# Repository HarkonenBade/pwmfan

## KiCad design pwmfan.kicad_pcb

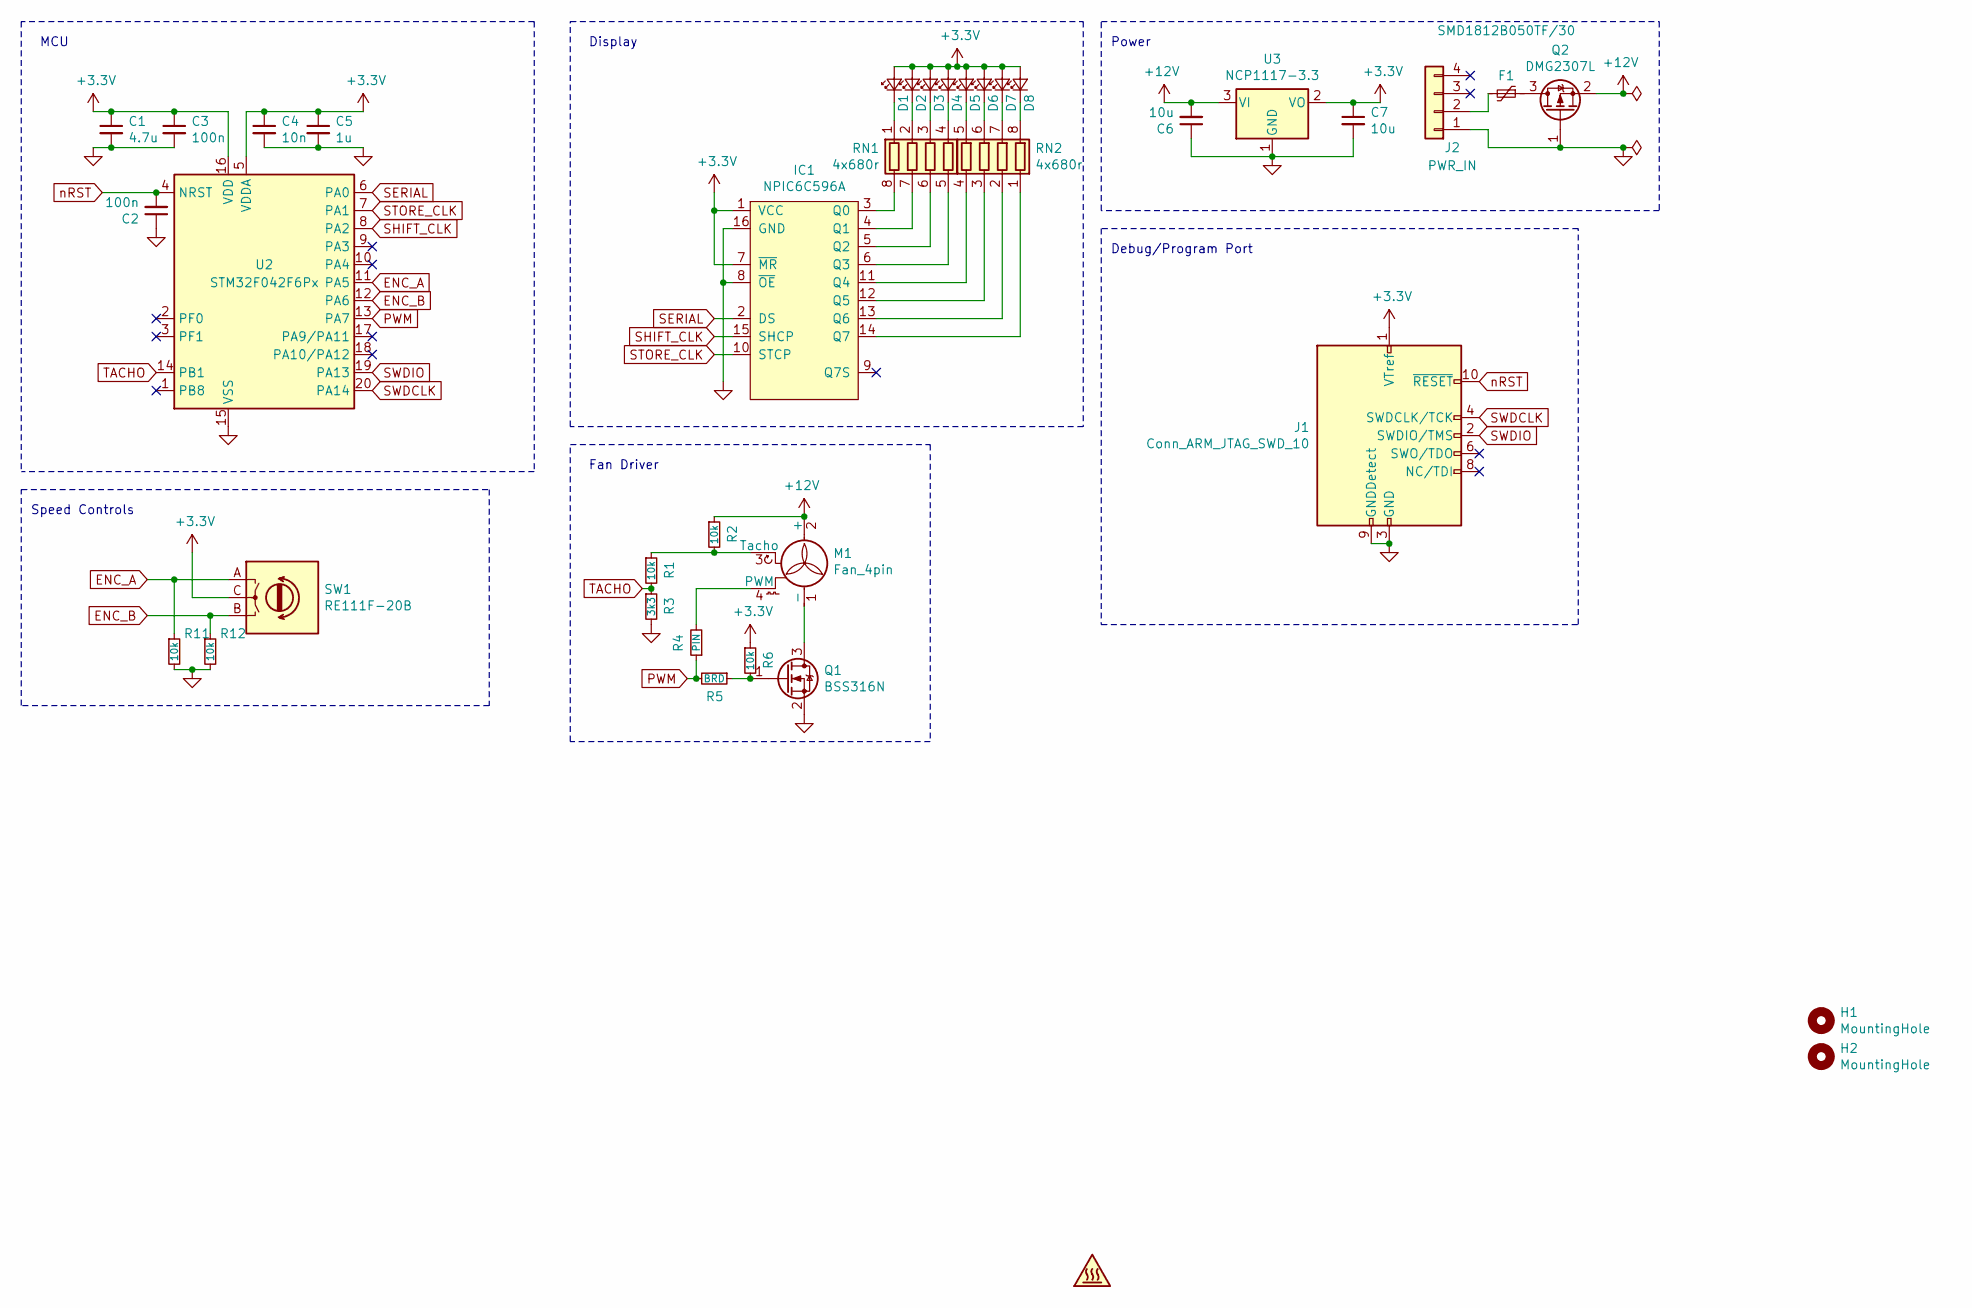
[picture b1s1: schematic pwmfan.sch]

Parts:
C1: 4.7u; C_0603_1608Metric
C2, C3: 100n; C_0603_1608Metric
C4: 10n; C_0603_1608Metric
C5: 1u; C_0603_1608Metric
C6, C7: 10u; C_0603_1608Metric
D1, D2, D3, D4, D5, D6, D7, D8: LED_Small; LED_D3.0mm_Horizontal_O1.27mm_Z2.0mm
F1: SMD1812B050TF/30; Fuse_1812_4532Metric; Farnell 3052512
H1, H2: MountingHole; MountingHole_3.2mm_M3_Pad
IC1: NPIC6C596A; TSSOP-16_4.4x5mm_P0.65mm; Farnell 2445196
J1: Conn_ARM_JTAG_SWD_10; PinHeader_2x05_P1.27mm_Vertical
J2: PWR_IN; Molex_KK-254_AE-6410-04A_1x04_P2.54mm_Vertical
M1: Fan_4pin; Molex_KK-254_AE-6410-04A_1x04_P2.54mm_Vertical
Q1: BSS316N; SOT-23; Farnell 2432720
Q2: DMG2307L; SOT-23; Farnell 2061518
R1, R2, R6, R11, R12: 10k; R_0603_1608Metric
R3: 3k3; R_0603_1608Metric
R4: PIN; R_0603_1608Metric
R5: BRD; R_0603_1608Metric
RN1, RN2: 4x680r; R_Array_Convex_4x0612
SW1: RE111F-20B
SYM1: QR
U2: STM32F042F6Px; TSSOP-20_4.4x6.5mm_P0.65mm
U3: NCP1117-3.3; SOT-223-3_TabPin2

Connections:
+3V3: C1.1, C3.1, C4.1, C5.1, C7.1, D1.2 (A), D2.2 (A), D3.2 (A), D4.2 (A), D5.2 (A), D6.2 (A), D7.2 (A), D8.2 (A), IC1.1 (VCC), IC1.7 (~MR), J1.1 (VTref), R6.1, SW1.C, U2.5 (VDDA), U2.16 (VDD), U3.2 (VO)
+12V: C6.2, M1.2 (+), Q2.2 (S), R2.1, U3.3 (VI)
ENC_A: R11.1, SW1.A, U2.11 (PA5)
ENC_B: R12.1, SW1.B, U2.12 (PA6)
GND: C1.2, C2.1, C3.2, C4.2, C5.2, C6.1, C7.2, IC1.8 (~OE), IC1.16 (GND), J1.3 (GND), J1.5 (GND), J1.9 (GNDDetect), J2.1, Q1.2 (S), Q2.1 (G), R3.2, R11.2, R12.2, U2.15 (VSS), U3.1 (GND)
unnamed: D1.1 (K), RN1.1 (R1.1)
unnamed: D2.1 (K), RN1.2 (R2.1)
unnamed: D3.1 (K), RN1.3 (R3.1)
unnamed: D4.1 (K), RN1.4 (R4.1)
unnamed: D5.1 (K), RN2.5 (R4.2)
unnamed: D6.1 (K), RN2.6 (R3.2)
unnamed: D7.1 (K), RN2.7 (R2.2)
unnamed: D8.1 (K), RN2.8 (R1.2)
unnamed: F1.1, Q2.3 (D)
unnamed: F1.2, J2.2
unnamed: IC1.3 (Q0), RN1.8 (R1.2)
unnamed: IC1.4 (Q1), RN1.7 (R2.2)
unnamed: IC1.5 (Q2), RN1.6 (R3.2)
unnamed: IC1.6 (Q3), RN1.5 (R4.2)
unnamed: IC1.11 (Q4), RN2.4 (R4.1)
unnamed: IC1.12 (Q5), RN2.3 (R3.1)
unnamed: IC1.13 (Q6), RN2.2 (R2.1)
unnamed: IC1.14 (Q7), RN2.1 (R1.1)
unnamed: M1.1 (-), Q1.3 (D)
unnamed: M1.3 (Tacho), R1.1, R2.2
unnamed: M1.4 (PWM), R4.2
unnamed: Q1.1 (G), R5.1, R6.2
PWM: R4.1, R5.2, U2.13 (PA7)
SERIAL: IC1.2 (DS), U2.6 (PA0)
SHIFT_CLK: IC1.15 (SHCP), U2.8 (PA2)
STORE_CLK: IC1.10 (STCP), U2.7 (PA1)
SWDCLK: J1.4 (SWDCLK/TCK), U2.20 (PA14)
SWDIO: J1.2 (SWDIO/TMS), U2.19 (PA13)
TACHO: R1.2, R3.1, U2.14 (PB1)
nRST: C2.2, J1.10 (~RESET~), U2.4 (NRST)

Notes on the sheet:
MCU
Debug/Program Port
Power
Speed Controls
Fan Driver
Display

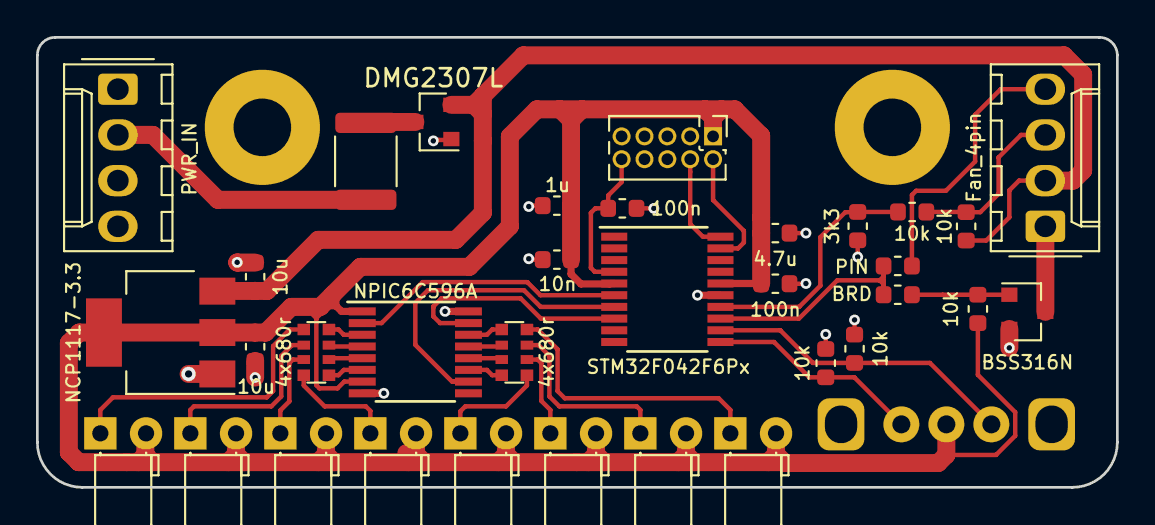
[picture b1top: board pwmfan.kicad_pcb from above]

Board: 2 copper layers, 60.0 x 25.0 mm, 38 parts (1 on the bottom side), 35 nets.

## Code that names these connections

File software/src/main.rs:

#![no_main]
#![no_std]

#[allow(unused)]
use panic_halt;

use stm32f0xx_hal as hal;

use cortex_m_rt::entry;

use crate::hal::{delay::Delay, prelude::*, stm32};

use cortex_m::peripheral::Peripherals;

use rotary_encoder_hal::{Direction, Rotary};

use embedded_hal::digital::v2::OutputPin;

struct ShiftReg<Ser: OutputPin, Shift: OutputPin, Store: OutputPin>{
    ser: Ser,
    shift: Shift,
    store: Store,
}

impl<Ser: OutputPin, Shift: OutputPin, Store: OutputPin> ShiftReg<Ser, Shift, Store> {
    fn new(ser: Ser, shift: Shift, store: Store) -> ShiftReg<Ser, Shift, Store> {
        ShiftReg {
            ser, shift, store
        }
    }

    fn fill(&mut self, items: impl IntoIterator<Item=bool>) {
        self.store.set_low().ok();
        for item in items {
            self.shift.set_low().ok();
            if item {
                self.ser.set_high().ok();
            } else {
                self.ser.set_low().ok();
            }
            self.shift.set_high().ok();
        }
        self.store.set_high().ok();
    }
}


#[entry]
fn main() -> ! {
    if let (Some(mut p), Some(cp)) = (stm32::Peripherals::take(), Peripherals::take()) {
        let (mut pwm, mut delay, mut leds, mut rot) = cortex_m::interrupt::free(|cs| {
            // Configure clock to 8 MHz (i.e. the default) and freeze it
            let mut rcc = p.RCC.configure().sysclk(8.mhz()).freeze(&mut p.FLASH);

            // Obtain resources from GPIO port A
            let gpioa = p.GPIOA.split(&mut rcc);

            let pwm = gpioa.pa7.into_alternate_af1(cs);

            // Shift Reg
            let ser = gpioa.pa0.into_push_pull_output(cs);
            let store = gpioa.pa1.into_push_pull_output(cs);
            let shift = gpioa.pa2.into_push_pull_output(cs);

            let leds = ShiftReg::new(ser, shift, store);

            // Get delay provider
            let delay = Delay::new(cp.SYST, &rcc);

            // Rotary Encoder
            let rot_a = gpioa.pa5.into_pull_down_input(cs);
            let rot_b = gpioa.pa6.into_pull_down_input(cs);

            let rot = Rotary::new(rot_a, rot_b);

            (pwm, delay, leds, rot)
        });

        let mut cnt: u16 = 0;

        loop {
            match rot.update().unwrap() {
                Direction::Clockwise => {
                    cnt += 1;
                }
                Direction::CounterClockwise => {
                    cnt -= 1;
                }
                Direction::None => { delay.delay_ms(1_u8) }
            }

            let v = cnt/4;
            let render = (0..8).into_iter().map(|i| ((v+1)/2) >= i+1).rev();
            leds.fill(render);
        }
    }

    loop {
        continue;
    }
}

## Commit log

2020-02-10 Base board files
2020-02-16 Various tweaks and adding more LEDs
2020-02-26 Various updates and silks
2020-02-26 Gerbers and other generated files
2020-03-01 Minor tweaks before shipping
2020-03-01 Regen files
